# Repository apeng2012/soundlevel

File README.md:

# soundlevel
sound level meter is based on KL25

http://www.amobbs.com/thread-5611291-1-1.html

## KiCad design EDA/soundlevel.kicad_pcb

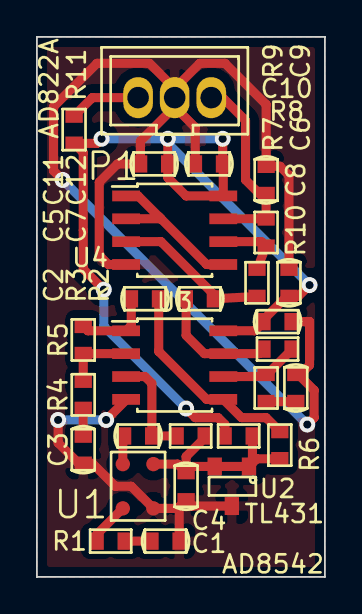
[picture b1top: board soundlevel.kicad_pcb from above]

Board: 2 copper layers, 16.0 x 30.0 mm, 28 parts (0 on the bottom side), 19 nets.

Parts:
C1: 0; SMD-0603_C
C2, C4, C5, C7, C8, C9, C11: 10u; SMD-0603_C
C3, C6: 2u; SMD-0603_C
C10, C12: 0.1u; SMD-0603_C
P1: CONN_01X03; PH-3A
R1, R11: 0; SMD-0603_R
R2: 1k; SMD-0603_R
R3, R5, R6, R8, R9, R10: 100k; SMD-0603_R
R4, R7: 10k; SMD-0603_R
U1: SPU0410HR5H; SPU04
U2: TL431; SOT-23
U3: AD8542; SOIC-8_3.9x4.9mm_Pitch1.27mm
U4: AD822A; SOIC-8_3.9x4.9mm_Pitch1.27mm

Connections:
+2V5: C4.2, R2.2, R3.2, R6.2, U1.1, U2.1, U2.2
+5V: C9.2, C10.2, C11.2, C12.2, R2.1, R11.2, U3.8, U4.8
GND: C1.1, C3.1, C4.1, C6.1, C8.1, C9.1, C10.1, C11.1, C12.1, P1.2, U1.2, U2.3, U3.4, U4.4
unnamed: C1.2, R1.1
unnamed: C2.1, R3.1, U3.3
unnamed: C2.2, U1.4
unnamed: C3.2, R4.1
unnamed: C5.1, R6.1, U3.5
unnamed: C5.2, R5.1, U3.1
unnamed: C6.2, R7.1
unnamed: C7.1, R9.2, U4.3
unnamed: C7.2, R8.1, U3.7
unnamed: C8.2, P1.3, R10.1, U4.7
unnamed: P1.1, R11.1
unnamed: R1.2, U1.3
unnamed: R4.2, R5.2, U3.2
unnamed: R7.2, R8.2, U3.6
unnamed: R9.1, R10.2, U4.6
unnamed: U4.1, U4.2, U4.5

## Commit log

2015-01-08 Update README.md
    add project URL
2015-01-08 plot gerber
2015-01-22 import uart example
2015-01-26 add ADC example
2015-01-30 pit trigger adc
2015-01-30 GBK->utf8
2015-02-02 adc dma
2015-02-04 get SPL
